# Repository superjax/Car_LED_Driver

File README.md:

# LED Driver Board

## Description
This repo contains one-sided eagle files that can be used to build an LED Driver circuit for a car.  The idea is to first low-pass the signal coming from the head unit, with a simple capacitor and resistor circuit.  I found that I sometime wanted to adjust my crossover frequency, so I have used a potentiometer in the place of the low-pass resistor.

After filtering, the signal is amplified 100x and used to drive a MOSFET which acts as a switch to turn off and on the LED's.  Video of this working can be found here (link coming soon).

I have only included the schematic and the board files.

## License
Copyright (c) 2015, James Jackson
All rights reserved

Redistribution and use in source and binary forms, with or without modification, are permitted provided that the following conditions are met:

1. Redistributions of source code must retain the above copyright notice, this list of conditions and the following disclaimer.

2. Redistributions in binary form must reproduce the above copyright notice, this list of conditions and the following disclaimer in the documentation and/or other materials provided with the distribution.

3. Neither the name of the copyright holder nor the names of its contributors may be used to endorse or promote products derived from this software without specific prior written permission.

THIS SOFTWARE IS PROVIDED BY THE COPYRIGHT HOLDERS AND CONTRIBUTORS "AS IS" AND ANY EXPRESS OR IMPLIED WARRANTIES, INCLUDING, BUT NOT LIMITED TO, THE IMPLIED WARRANTIES OF MERCHANTABILITY AND FITNESS FOR A PARTICULAR PURPOSE ARE DISCLAIMED. IN NO EVENT SHALL THE COPYRIGHT HOLDER OR CONTRIBUTORS BE LIABLE FOR ANY DIRECT, INDIRECT, INCIDENTAL, SPECIAL, EXEMPLARY, OR CONSEQUENTIAL DAMAGES (INCLUDING, BUT NOT LIMITED TO, PROCUREMENT OF SUBSTITUTE GOODS OR SERVICES; LOSS OF USE, DATA, OR PROFITS; OR BUSINESS INTERRUPTION) HOWEVER CAUSED AND ON ANY THEORY OF LIABILITY, WHETHER IN CONTRACT, STRICT LIABILITY, OR TORT (INCLUDING NEGLIGENCE OR OTHERWISE) ARISING IN ANY WAY OUT OF THE USE OF THIS SOFTWARE, EVEN IF ADVISED OF THE POSSIBILITY OF SUCH DAMAGE.

<script>
  (function(i,s,o,g,r,a,m){i['GoogleAnalyticsObject']=r;i[r]=i[r]||function(){
  (i[r].q=i[r].q||[]).push(arguments)},i[r].l=1*new Date();a=s.createElement(o),
  m=s.getElementsByTagName(o)[0];a.async=1;a.src=g;m.parentNode.insertBefore(a,m)
  })(window,document,'script','//www.google-analytics.com/analytics.js','ga');

  ga('create', 'UA-55384642-6', 'auto');
  ga('send', 'pageview');

</script>

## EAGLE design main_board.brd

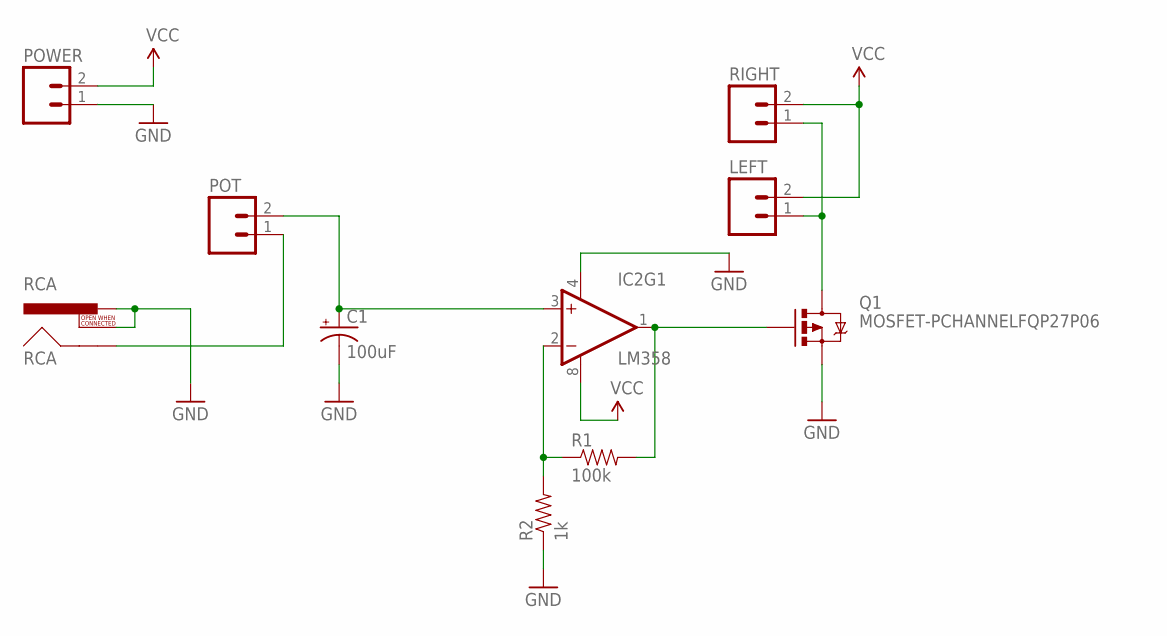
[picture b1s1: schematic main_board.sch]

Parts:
C1: 100uF; CPOL-RADIAL-100UF-25V
IC2: LM358; DIP08
LEFT: M02PTH; 1X02
POT: M02PTH; 1X02
POWER: M02PTH; 1X02
Q1: MOSFET-PCHANNELFQP27P06; TO220V
R1: 100k; AXIAL-0.3-KIT
R2: 1k; AXIAL-0.3-KIT
RCA: RCA
RIGHT: M02PTH; 1X02

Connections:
AUDIO_SIGNAL: POT.1, RCA.SHELL
GND: C1.2 (-), IC2.4 (V-), POWER.1, Q1.3 (S), R2.P$1 (1), RCA.PIN, RCA.SWITCH
unnamed: C1.1 (+), IC2.3 (+IN), POT.2
unnamed: IC2.1 (OUT), Q1.1 (G), R1.P$2 (2)
unnamed: IC2.2 (-IN), R1.P$1 (1), R2.P$2 (2)
unnamed: LEFT.1, Q1.2 (D), RIGHT.1
VCC: IC2.8 (V+), LEFT.2, POWER.2, RIGHT.2

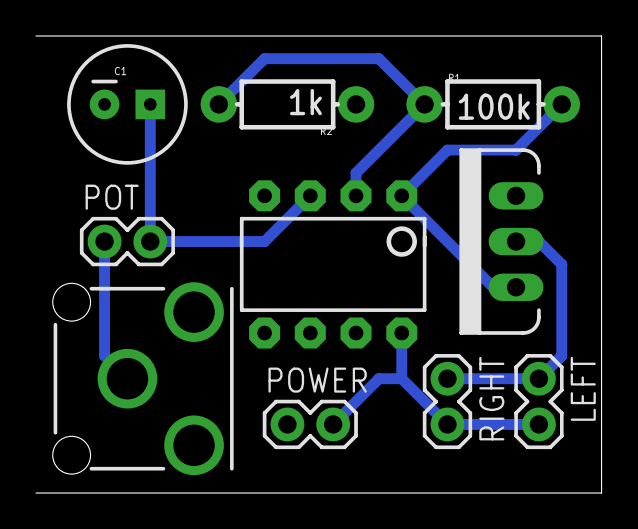
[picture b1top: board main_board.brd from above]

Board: 2 copper layers, 31.4 x 25.4 mm, 10 parts (0 on the bottom side), 7 nets.

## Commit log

2015-05-15 added license, initial git upload
2015-05-15 Corrected Typo
2015-05-21 removed gerbers

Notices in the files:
parts and their libraries:
SparkFun-Connectors: Licensing: Creative Commons ShareAlike 4.0 International - https://creativecommons.org/licenses/by-sa/4.0
